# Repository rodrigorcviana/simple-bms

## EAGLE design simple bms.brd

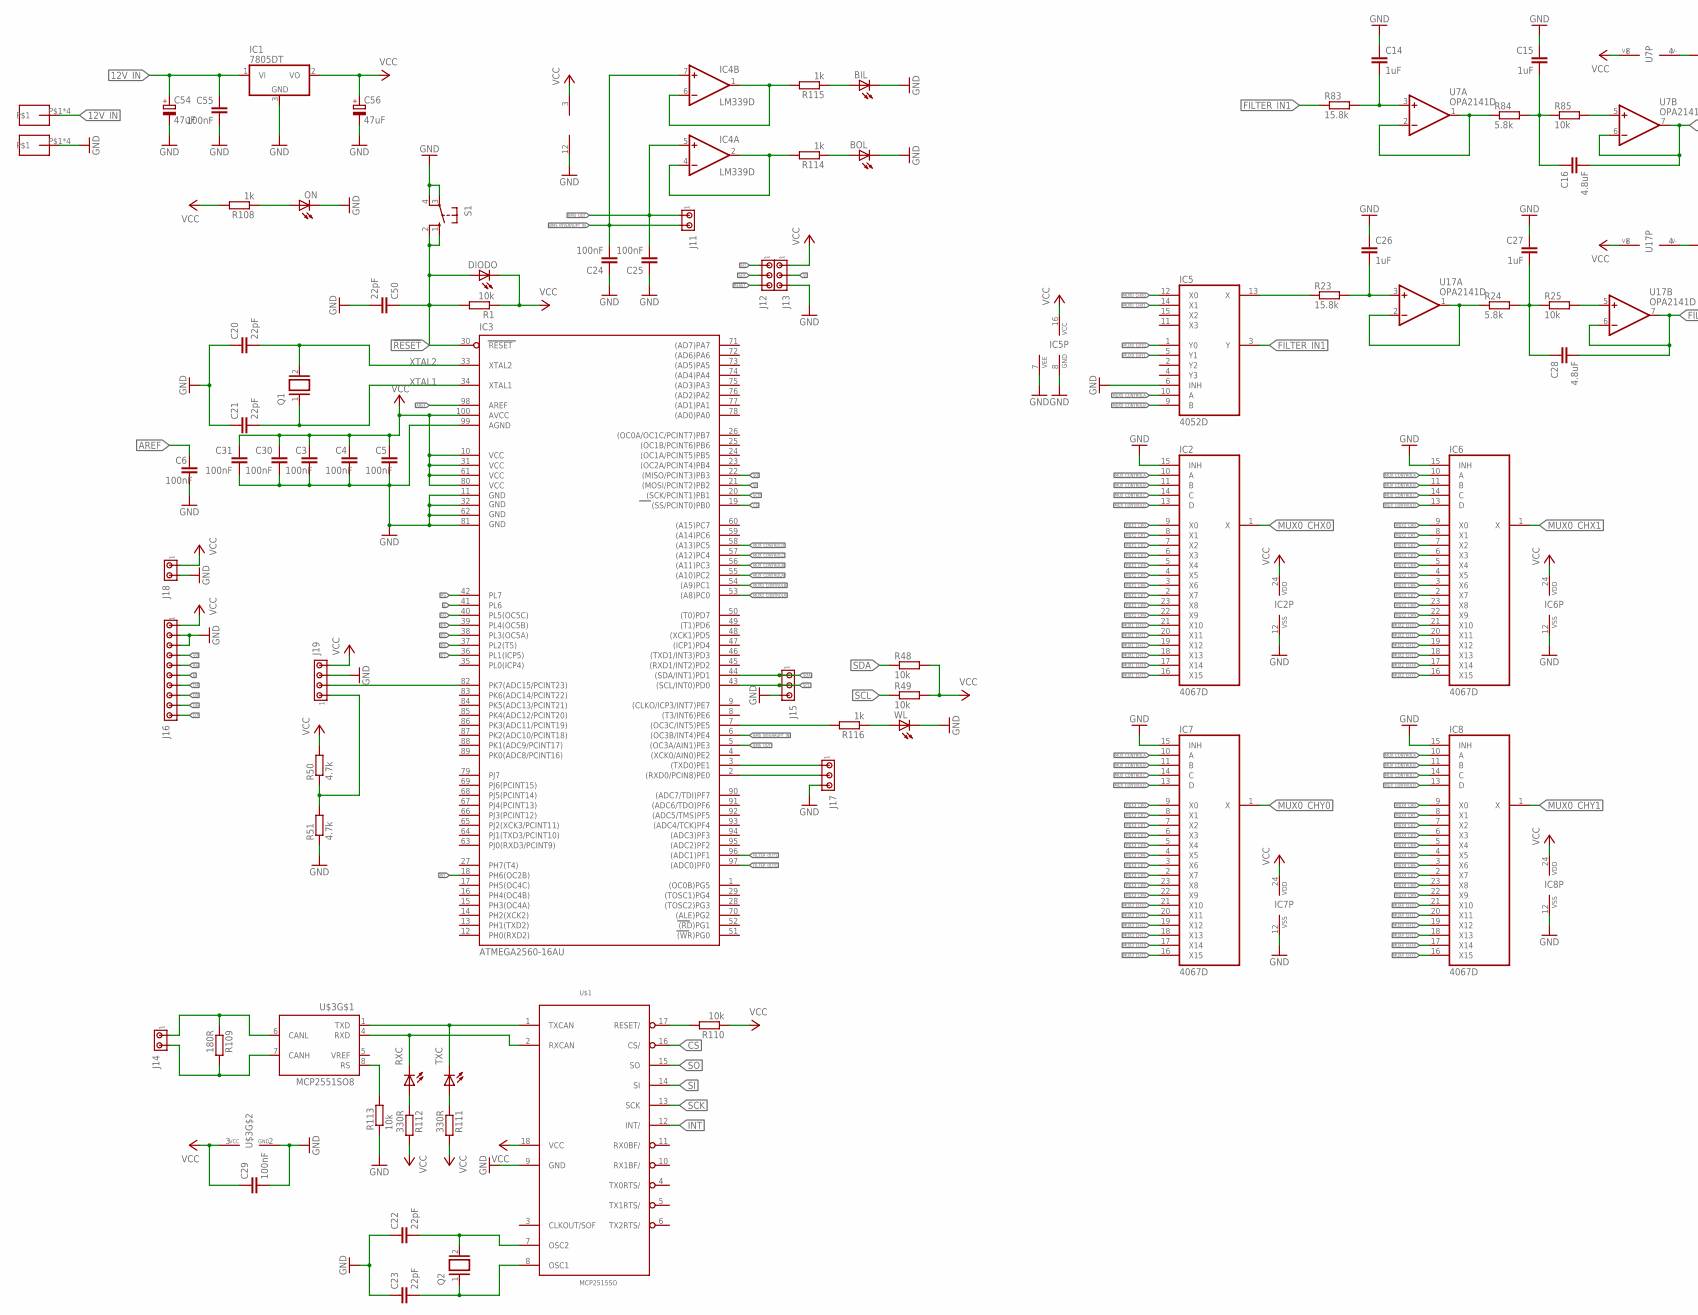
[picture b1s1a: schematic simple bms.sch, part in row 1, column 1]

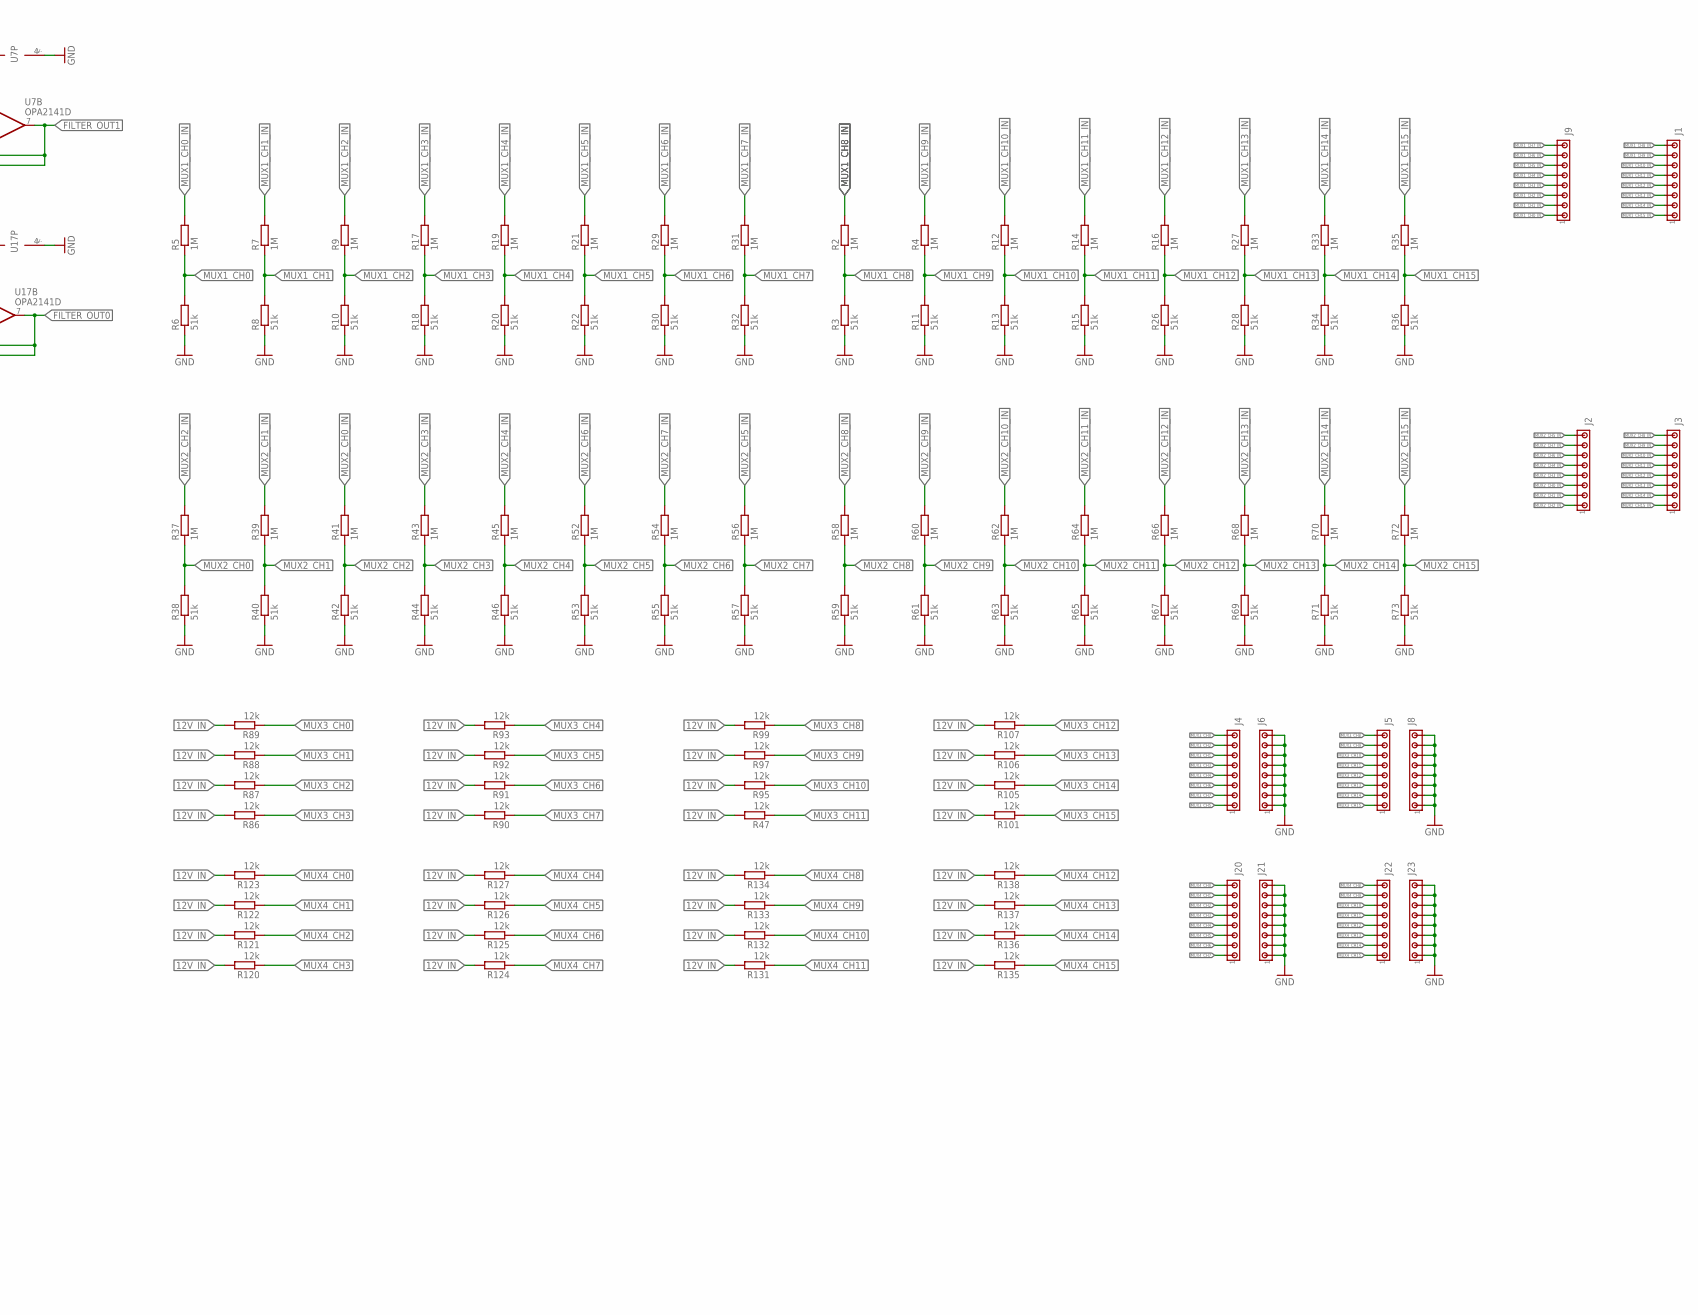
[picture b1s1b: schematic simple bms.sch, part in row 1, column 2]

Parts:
BIL: LEDCHIPLED_0805; CHIPLED_0805
BOL: LEDCHIPLED_0805; CHIPLED_0805
C3, C4, C5, C6, C24, C25, C29, C30, C31, C55: 100nF; C0805
C14, C15, C26, C27: 1uF; C0805
C16, C28: 4.8uF; C0805
C20, C21, C22, C23, C50: 22pF; C0805
C54, C56: 47uF; E5-8,5
DIODO: LEDCHIPLED_1206; CHIPLED_1206
IC1: 7805DT; TO252
IC2, IC6, IC7, IC8: 4067D; SO24W
IC3: ATMEGA2560-16AU; TQFP100
IC4: LM339D; SO14
IC5: 4052D; SO16
J1, J2, J3, J4, J5, J6, J8, J9, J20, J21, J22, J23: MTA08-100; 10X08MTA
J11, J14, J18: MTA02-100; 10X02MTA
J12, J13, J15, J17: MTA03-100; 10X03MTA
J16: MTA10-100; 10X10MTA
J19: MTA04-100; 10X04MTA
ON: LEDCHIPLED_0805; CHIPLED_0805
Q1, Q2: XTAL/S; QS
R1, R25, R48, R49, R85, R110, R113: 10k; R0805
R2, R4, R5, R7, R9, R12, R14, R16, R17, R19, R21, R27, R29, R31, R33, R35, R37, R39, R41, R43, R45, R52, R54, R56, R58, R60, R62, R64, R66, R68, R70, R72: 1M; R0805
R3, R6, R8, R10, R11, R13, R15, R18, R20, R22, R26, R28, R30, R32, R34, R36, R38, R40, R42, R44, R46, R53, R55, R57, R59, R61, R63, R65, R67, R69, R71, R73: 51k; R0805
R23, R83: 15.8k; R0805
R24, R84: 5.8k; R0805
R47, R86, R87, R88, R89, R90, R91, R92, R93, R95, R97, R99, R101, R105, R106, R107, R120, R121, R122, R123, R124, R125, R126, R127, R131, R132, R133, R134, R135, R136, R137, R138: 12k; R0805
R50, R51: 4.7k; R0805
R108, R114, R115, R116: 1k; R0805
R109: 180R; R0805
R111, R112: 330R; R0805
RXC: LEDCHIPLED_0805; CHIPLED_0805
S1: 40-XX; B3F-40XX
TXC: LEDCHIPLED_0805; CHIPLED_0805
U7, U17: OPA2141D; SO08
U$1: MCP2515SO; SO18L
U$2, U$4: SCREWCONECTOR
U$3: MCP2551SO8; SO08
WL: LEDCHIPLED_0805; CHIPLED_0805

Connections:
12V_IN: C54.+, C55.1, IC1.1 (VI), R47.2, R86.2, R87.2, R88.2, R89.2, R90.2, R91.2, R92.2, R93.2, R95.2, R97.2, R99.2, R101.2, R105.2, R106.2, R107.2, R120.2, R121.2, R122.2, R123.2, R124.2, R125.2, R126.2, R127.2, R131.2, R132.2, R133.2, R134.2, R135.2, R136.2, R137.2, R138.2, U$2.P$1, U$2.P$2, U$2.P$3, U$2.P$4
!RESET: C50.1, DIODO.A, IC3.30 (RESET), J12.3, R1.2, S1.1 (S), S1.2 (S1)
AREF: C6.1, IC3.98 (AREF)
BMS_INTERRUPT_IN: C24.2, IC3.6 ((OC3B/INT4)PE4), IC4.7 (+IN), J11.2
BMS_OUT: C25.2, IC3.5 ((OC3A/AIN1)PE3), IC4.5 (+IN), J11.1
CS: IC3.19 ((SS/PCINT0)PB0), U$1.16 (CS/)
D4: IC3.39 (PL4(OC5B)), J16.7
D5: IC3.38 (PL3(OC5A)), J16.8
D6: IC3.37 (PL2(T5)), J16.9
D7: IC3.36 (PL1(ICP5)), J16.10
E: IC3.41 (PL6), J16.6
FILTER_IN1: IC5.3 (Y), R83.1
FILTER_OUT0: C28.2, IC3.97 ((ADC0)PF0), U17.6 (-IN), U17.7 (OUT)
FILTER_OUT1: C16.2, IC3.96 ((ADC1)PF1), U7.6 (-IN), U7.7 (OUT)
GND: BIL.C, BOL.C, C3.2, C4.2, C5.2, C6.2, C14.1, C15.1, C20.1, C21.1, C22.1, C23.1, C24.1, C25.1, C26.1, C27.1, C29.2, C30.2, C31.2, C50.2, C54.-, C55.2, C56.-, IC1.3 (GND), IC2.12 (VSS), IC2.15 (INH), IC3.11 (GND), IC3.32 (GND1), IC3.62 (GND2), IC3.81 (GND3), IC3.99 (AGND), IC4.12 (GND), IC5.6 (INH), IC5.7 (VEE), IC5.8 (GND), IC6.12 (VSS), IC6.15 (INH), IC7.12 (VSS), IC7.15 (INH), IC8.12 (VSS), IC8.15 (INH), J6.1, J6.2, J6.3, J6.4, J6.5, J6.6, J6.7, J6.8, J8.1, J8.2, J8.3, J8.4, J8.5, J8.6, J8.7, J8.8, J13.3, J15.3, J16.2, J16.3, J17.3, J18.2, J19.3, J21.1, J21.2, J21.3, J21.4, J21.5, J21.6, J21.7, J21.8, J23.1, J23.2, J23.3, J23.4, J23.5, J23.6, J23.7, J23.8, ON.C, R3.1, R6.1, R8.1, R10.1, R11.1, R13.1, R15.1, R18.1, R20.1, R22.1, R26.1, R28.1, R30.1, R32.1, R34.1, R36.1, R38.1, R40.1, R42.1, R44.1, R46.1, R51.1, R53.1, R55.1, R57.1, R59.1, R61.1, R63.1, R65.1, R67.1, R69.1, R71.1, R73.1, R113.1, S1.3, S1.4 (P1), U7.4 (V-), U17.4 (V-), U$1.9 (GND), U$3.2 (GND), U$4.P$1, U$4.P$2, U$4.P$3, U$4.P$4, WL.C
INT: IC3.18 (PH6(OC2B)), U$1.12 (INT/)
MUX0_CHX0: IC2.1 (X), IC5.12 (X0)
MUX0_CHX1: IC5.14 (X1), IC6.1 (X)
MUX0_CHY0: IC5.1 (Y0), IC7.1 (X)
MUX0_CHY1: IC5.5 (Y1), IC8.1 (X)
MUX0_CONTROLA: IC3.53 ((A8)PC0), IC5.10 (A)
MUX0_CONTROLB: IC3.54 ((A9)PC1), IC5.9 (B)
MUX1_CH0: IC2.9 (X0), R5.1, R6.2
MUX1_CH0_IN: J9.1, R5.2
MUX1_CH1: IC2.8 (X1), R7.1, R8.2
MUX1_CH1_IN: J9.2, R7.2
MUX1_CH2: IC2.7 (X2), R9.1, R10.2
MUX1_CH2_IN: J9.3, R9.2
MUX1_CH3: IC2.6 (X3), R17.1, R18.2
MUX1_CH3_IN: J9.4, R17.2
MUX1_CH4: IC2.5 (X4), R19.1, R20.2
MUX1_CH4_IN: J9.5, R19.2
MUX1_CH5: IC2.4 (X5), R21.1, R22.2
MUX1_CH5_IN: J9.6, R21.2
MUX1_CH6: IC2.3 (X6), R29.1, R30.2
MUX1_CH6_IN: J9.7, R29.2
MUX1_CH7: IC2.2 (X7), R31.1, R32.2
MUX1_CH7_IN: J9.8, R31.2
MUX1_CH8: IC2.23 (X8), R2.1, R3.2
MUX1_CH8_IN: J1.8, R2.2
MUX1_CH9: IC2.22 (X9), R4.1, R11.2
MUX1_CH9_IN: J1.7, R4.2
MUX1_CH10: IC2.21 (X10), R12.1, R13.2
MUX1_CH10_IN: J1.6, R12.2
MUX1_CH11: IC2.20 (X11), R14.1, R15.2
MUX1_CH11_IN: J1.5, R14.2
MUX1_CH12: IC2.19 (X12), R16.1, R26.2
MUX1_CH12_IN: J1.4, R16.2
MUX1_CH13: IC2.18 (X13), R27.1, R28.2
MUX1_CH13_IN: J1.3, R27.2
MUX1_CH14: IC2.17 (X14), R33.1, R34.2
MUX1_CH14_IN: J1.2, R33.2
MUX1_CH15: IC2.16 (X15), R35.1, R36.2
MUX1_CH15_IN: J1.1, R35.2
MUX2_CH0: IC6.9 (X0), R37.1, R38.2
MUX2_CH0_IN: J2.3, R41.2
MUX2_CH1: IC6.8 (X1), R39.1, R40.2
MUX2_CH1_IN: J2.2, R39.2
MUX2_CH2: IC6.7 (X2), R41.1, R42.2
MUX2_CH2_IN: J2.1, R37.2
MUX2_CH3: IC6.6 (X3), R43.1, R44.2
MUX2_CH3_IN: J2.4, R43.2
MUX2_CH4: IC6.5 (X4), R45.1, R46.2
MUX2_CH4_IN: J2.5, R45.2
MUX2_CH5: IC6.4 (X5), R52.1, R53.2
MUX2_CH5_IN: J2.8, R56.2
MUX2_CH6: IC6.3 (X6), R54.1, R55.2
MUX2_CH6_IN: J2.6, R52.2
MUX2_CH7: IC6.2 (X7), R56.1, R57.2
MUX2_CH7_IN: J2.7, R54.2
MUX2_CH8: IC6.23 (X8), R58.1, R59.2
MUX2_CH8_IN: J3.8, R58.2
MUX2_CH9: IC6.22 (X9), R60.1, R61.2
MUX2_CH9_IN: J3.7, R60.2
MUX2_CH10: IC6.21 (X10), R62.1, R63.2
MUX2_CH10_IN: J3.6, R62.2
MUX2_CH11: IC6.20 (X11), R64.1, R65.2
MUX2_CH11_IN: J3.5, R64.2
MUX2_CH12: IC6.19 (X12), R66.1, R67.2
MUX2_CH12_IN: J3.4, R66.2
MUX2_CH13: IC6.18 (X13), R68.1, R69.2
MUX2_CH13_IN: J3.3, R68.2
MUX2_CH14: IC6.17 (X14), R70.1, R71.2
MUX2_CH14_IN: J3.2, R70.2
MUX2_CH15: IC6.16 (X15), R72.1, R73.2
MUX2_CH15_IN: J3.1, R72.2
MUX3_CH0: IC7.9 (X0), J4.8, R89.1
MUX3_CH1: IC7.7 (X2), J4.6, R88.1
MUX3_CH2: IC7.8 (X1), J4.7, R87.1
MUX3_CH3: IC7.6 (X3), J4.5, R86.1
MUX3_CH4: IC7.5 (X4), J4.4, R93.1
MUX3_CH5: IC7.2 (X7), J4.1, R92.1
MUX3_CH6: IC7.4 (X5), J4.3, R91.1
MUX3_CH7: IC7.3 (X6), J4.2, R90.1
MUX3_CH8: IC7.23 (X8), J5.8, R99.1
MUX3_CH9: IC7.22 (X9), J5.7, R97.1
MUX3_CH10: IC7.21 (X10), J5.6, R95.1
MUX3_CH11: IC7.20 (X11), J5.5, R47.1
MUX3_CH12: IC7.19 (X12), J5.4, R107.1
MUX3_CH13: IC7.18 (X13), J5.3, R106.1
MUX3_CH14: IC7.17 (X14), J5.2, R105.1
MUX3_CH15: IC7.16 (X15), J5.1, R101.1
MUX4_CH0: IC8.9 (X0), J20.8, R123.1
MUX4_CH1: IC8.8 (X1), J20.7, R122.1
MUX4_CH2: IC8.7 (X2), J20.6, R121.1
MUX4_CH3: IC8.6 (X3), J20.5, R120.1
MUX4_CH4: IC8.5 (X4), J20.4, R127.1
MUX4_CH5: IC8.4 (X5), J20.3, R126.1
MUX4_CH6: IC8.3 (X6), J20.2, R125.1
MUX4_CH7: IC8.2 (X7), J20.1, R124.1
MUX4_CH8: IC8.23 (X8), J22.8, R134.1
MUX4_CH9: IC8.22 (X9), J22.7, R133.1
MUX4_CH10: IC8.21 (X10), J22.6, R132.1
MUX4_CH11: IC8.20 (X11), J22.5, R131.1
MUX4_CH12: IC8.19 (X12), J22.4, R138.1
MUX4_CH13: IC8.18 (X13), J22.3, R137.1
MUX4_CH14: IC8.17 (X14), J22.2, R136.1
MUX4_CH15: IC8.16 (X15), J22.1, R135.1
MUX_CONTROLA: IC2.10 (A), IC3.55 ((A10)PC2), IC6.10 (A), IC7.10 (A), IC8.10 (A)
MUX_CONTROLB: IC2.11 (B), IC3.56 ((A11)PC3), IC6.11 (B), IC7.11 (B), IC8.11 (B)
MUX_CONTROLC: IC2.14 (C), IC3.57 ((A12)PC4), IC6.14 (C), IC7.14 (C), IC8.14 (C)
MUX_CONTROLD: IC2.13 (D), IC3.58 ((A13)PC5), IC6.13 (D), IC7.13 (D), IC8.13 (D)
unnamed: C14.2, R83.2, U7.3 (+IN)
unnamed: R84.1, U7.1 (OUT), U7.2 (-IN)
unnamed: C15.2, C16.1, R84.2, R85.1
unnamed: R85.2, U7.5 (+IN)
unnamed: R110.2, U$1.17 (RESET/)
unnamed: IC3.7 ((OC3C/INT5)PE5), R116.2
unnamed: J14.1, R109.1, U$3.6 (CANL)
unnamed: R111.1, TXC.A
unnamed: ON.A, R108.1
unnamed: R112.1, RXC.A
unnamed: IC4.2 (OUT), IC4.4 (-IN), R114.2
unnamed: IC4.1 (OUT), IC4.6 (-IN), R115.2
unnamed: BIL.A, R115.1
unnamed: BOL.A, R114.1
unnamed: R116.1, WL.A
unnamed: TXC.C, U$1.1 (TXCAN), U$3.1 (TXD)
unnamed: RXC.C, U$1.2 (RXCAN), U$3.4 (RXD)
unnamed: R113.2, U$3.8 (RS)
unnamed: J14.2, R109.2, U$3.7 (CANH)
unnamed: C26.2, R23.2, U17.3 (+IN)
unnamed: R24.1, U17.1 (OUT), U17.2 (-IN)
unnamed: C27.2, C28.1, R24.2, R25.1
unnamed: R25.2, U17.5 (+IN)
unnamed: IC5.13 (X), R23.1
unnamed: IC3.3 ((TXD0)PE1), J17.1
unnamed: IC3.82 (PK7(ADC15/PCINT23)), J19.2
unnamed: J19.1, R50.1, R51.2
unnamed: IC3.2 ((RXD0/PCIN8)PE0), J17.2
RS: IC3.42 (PL7), J16.5
SCK: IC3.20 ((SCK/PCINT1)PB1), J12.2, U$1.13 (SCK)
SCL: IC3.43 ((SCL/INT0)PD0), J15.2, R49.1
SDA: IC3.44 ((SDA/INT1)PD1), J15.1, R48.1
SI: IC3.21 ((MOSI/PCINT2)PB2), J13.2, U$1.14 (SI)
SO: IC3.22 ((MISO/PCINT3)PB3), J12.1, U$1.15 (SO)
V0: IC3.40 (PL5(OC5C)), J16.4
VCC: C3.1, C4.1, C5.1, C29.1, C30.1, C31.1, C56.+, DIODO.C, IC1.2 (VO), IC2.24 (VDD), IC3.10 (VCC), IC3.31 (VCC1), IC3.61 (VCC2), IC3.80 (VCC3), IC3.100 (AVCC), IC4.3 (V+), IC5.16 (VCC), IC6.24 (VDD), IC7.24 (VDD), IC8.24 (VDD), J13.1, J16.1, J18.1, J19.4, R1.1, R48.2, R49.2, R50.2, R108.2, R110.1, R111.2, R112.2, U7.8 (V+), U17.8 (V+), U$1.18 (VCC), U$3.3 (VCC)
XTAL1: C21.2, IC3.34 (XTAL1), Q1.1
XTAL2: C20.2, IC3.33 (XTAL2), Q1.2
XTAL3: C22.2, Q2.2, U$1.7 (OSC2)
XTAL4: C23.2, Q2.1, U$1.8 (OSC1)

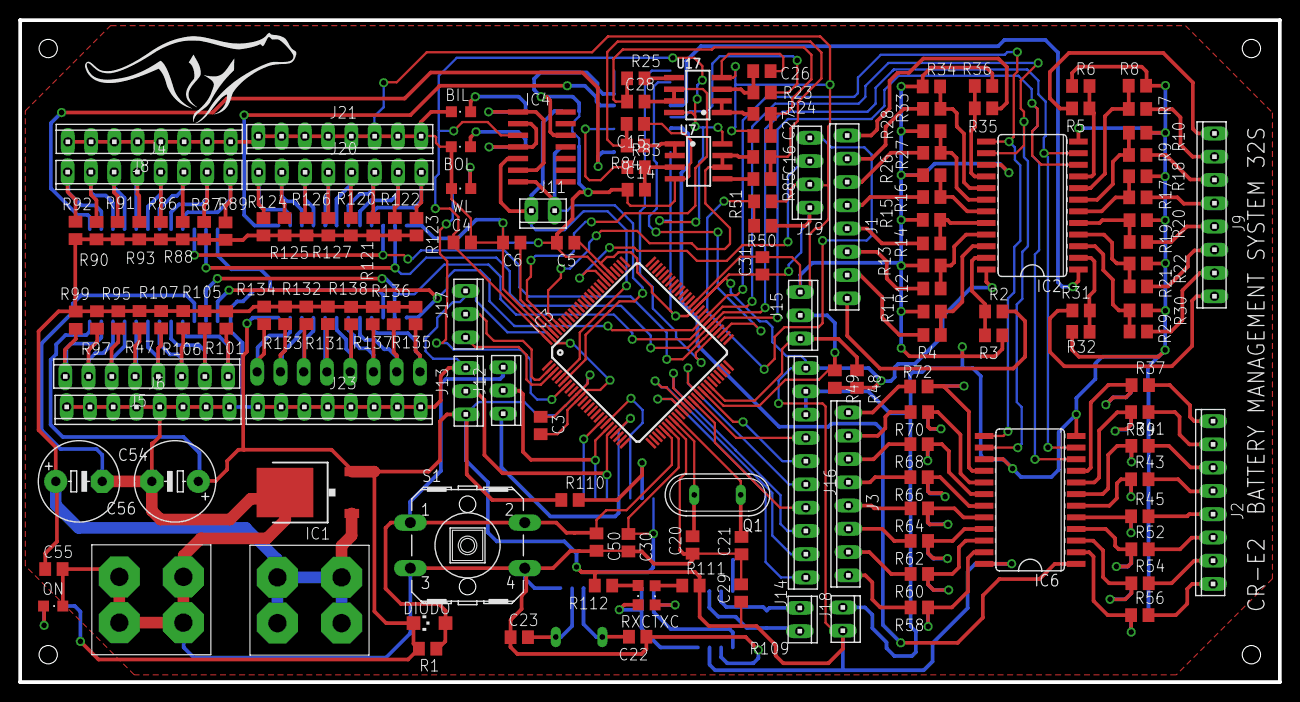
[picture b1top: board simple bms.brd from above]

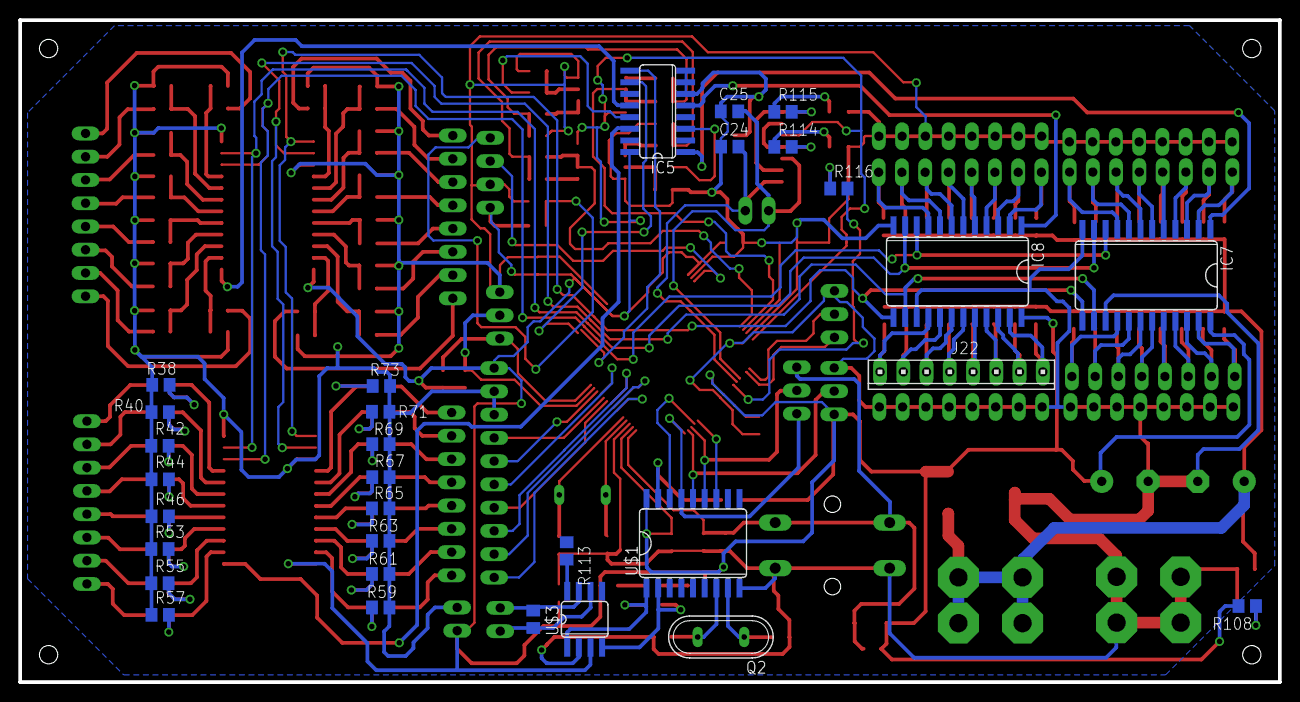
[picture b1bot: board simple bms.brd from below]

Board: 2 copper layers, 137.6 x 72.3 mm, 185 parts (31 on the bottom side), 162 nets.

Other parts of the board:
U$5: LOGOCHEETAH

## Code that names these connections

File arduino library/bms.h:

#ifndef BMS_H
#define BMS_H

#define MAX_CELULAS 34
#define MAX_PTC 12

#define MIN_TENSAO 2.79
#define MAX_TENSAO 3.63
#define WARNING_TENSAO 3.19
#define WARNING_TEMPERATURA 50

#define OFFSET_TEMPERATURA_VOLT -55

#define MAX_TEMPERATURA 60

#define VREF_HALL 2.5
#define IPN 400


class BMS{
private:

    boolean isMain;
    float temperaturaVolt[206] = {2.71567, 2.72464, 2.73359, 2.7455, 2.75441, 2.76627, 2.77514, 2.784, 2.79578, 2.8046,
                                  2.81633, 2.8251, 2.83678, 2.84552, 2.85424, 2.86584, 2.87452, 2.88608, 2.89472,
                                  2.90622, 2.91769, 2.92628, 2.9377, 2.94624, 2.95761, 2.96612, 2.97744, 2.98874,
                                  2.99719, 3.00843, 3.01684, 3.02804, 3.0392, 3.04756, 3.05868, 3.06977, 3.07807,
                                  3.08911, 3.10012, 3.10837, 3.11933, 3.13027, 3.14119, 3.14935, 3.16022, 3.17106,
                                  3.18187, 3.18997, 3.20073, 3.21147, 3.22219, 3.23288, 3.24354, 3.25152, 3.26214,
                                  3.27273, 3.28329, 3.29383, 3.30435, 3.31484, 3.3253, 3.33574, 3.34355, 3.35395,
                                  3.36432, 3.37466, 3.38498, 3.39528, 3.40555, 3.4158, 3.42602, 3.43622, 3.44639,
                                  3.45654, 3.46667, 3.47929, 3.48936, 3.49941, 3.50943, 3.51943, 3.52941, 3.53937,
                                  3.5493, 3.5592, 3.57155, 3.58141, 3.59124, 3.60105, 3.61084, 3.6206, 3.63277,
                                  3.64248, 3.65217, 3.66184, 3.67389, 3.68351, 3.69311, 3.70268, 3.71461, 3.72414,
                                  3.73364, 3.74549, 3.75494, 3.76437, 3.77613, 3.78551, 3.79487, 3.80654, 3.81586,
                                  3.82747, 3.83673, 3.84829, 3.85751, 3.8667, 3.87817, 3.88732, 3.89873, 3.90784,
                                  3.91919, 3.92825, 3.93955, 3.94856, 3.9598, 3.96877, 3.97995, 3.9911, 4, 4.0111,
                                  4.01995, 4.03099, 4.042, 4.05079, 4.06174, 4.07048, 4.08139, 4.09226, 4.10093,
                                  4.11175, 4.12254, 4.1333, 4.14188, 4.15259, 4.16327, 4.17391, 4.18241, 4.19301,
                                  4.20357, 4.21411, 4.22252, 4.23301, 4.24347, 4.2539, 4.2643, 4.27468, 4.28503,
                                  4.29328, 4.30358, 4.31385, 4.32409, 4.33431, 4.3445, 4.35466, 4.36479, 4.3749,
                                  4.38498, 4.39504, 4.40506, 4.41506, 4.42504, 4.43499, 4.44491, 4.45481, 4.46468,
                                  4.47452, 4.48434, 4.49414, 4.5039, 4.51559, 4.5253, 4.53499, 4.54465, 4.55429,
                                  4.5639, 4.57349, 4.58496, 4.5945, 4.60401, 4.61349, 4.62484, 4.63427, 4.64368,
                                  4.65306, 4.66429, 4.67362, 4.68293, 4.69221, 4.70332, 4.71255, 4.72176, 4.73278,
                                  4.74194, 4.75289, 4.762, 4.77108, 4.78195, 4.79099};
    float celula[34];
    float _celula[34]
    int temp[12];
    int _temp[12];
    float corrente;
    float tensaoTotal;
    int temperaturaMedia

    const int MUX0_CONTROLA = 37;
    const int MUX0_CONTROLB = 36;
    const int MUX0_CONTROLC = 35;

    const int MUX1_CONTROLA = 34;
    const int MUX1_CONTROLB = 33;
    const int MUX1_CONTROLC = 32;

    const int MUX2_CONTROLA = 31;
    const int MUX2_CONTROLB = 30;
    const int MUX2_CONTROLC = 10;

    const int MUX3_CONTROLA = 11;
    const int MUX3_CONTROLB = 12;
    const int MUX3_CONTROLC = 13;

    const int MUX4_CONTROLA = 41;
    const int MUX4_CONTROLB = 40;
    const int MUX4_CONTROLC = 39;

    const int MUX5_CONTROLA = 6;
    const int MUX5_CONTROLB = 7;
    const int MUX5_CONTROLC = 8;

    const int FILTER_OUT0 = A0;
    const int FILTER_OUT1 = A1;
    const int FILTER_OUT2 = A2;
    const int FILTER_OUT3 = A3;
    const int FILTER_OUT4 = A4;
    const int FILTER_OUT5 = A5;
    const int HALL = A15;

    const int BMS_OUT = 5;
    const int WARNING_LED = 3;

    const int V0 = 44;

    LiquidCrystal lcd(5, 6, 7, 8, 9, 10);
    MCP_CAN CAN0(53);

private:
    void setChannel(int, int);
    int adcRead(int);
    void warning();
    void tError();

public:
    void BMS(boolean);
    void begin();
    void read();
    float getTensao(int);
    float getCorrente();
    int getTemperatura(int);
    //void check();
    void CANReceive();
    void CANSend();
    void DisplayReceive();
    void DisplaySend();
    float getTensaoTotal();
    float getTensaoMedia();
    int getTemperaturaMedia();

};

#endif // BMS_H

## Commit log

2021-04-13 project files
2021-04-13 update files

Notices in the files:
parts and their libraries:
amp-op: Copyright (C) 2015, Bob Starr
